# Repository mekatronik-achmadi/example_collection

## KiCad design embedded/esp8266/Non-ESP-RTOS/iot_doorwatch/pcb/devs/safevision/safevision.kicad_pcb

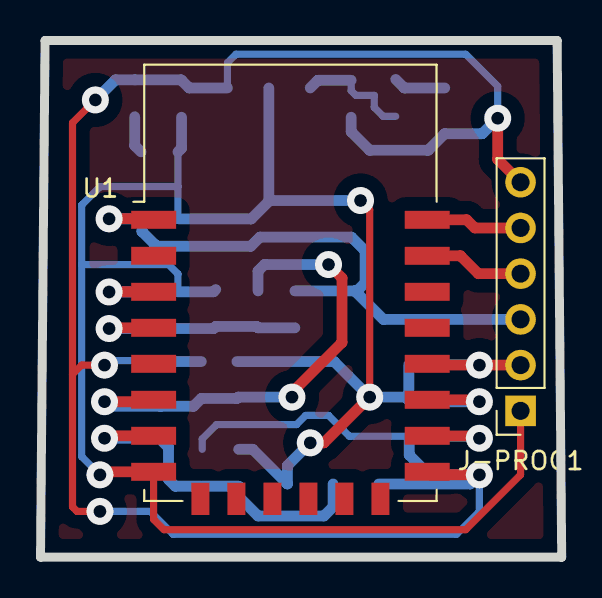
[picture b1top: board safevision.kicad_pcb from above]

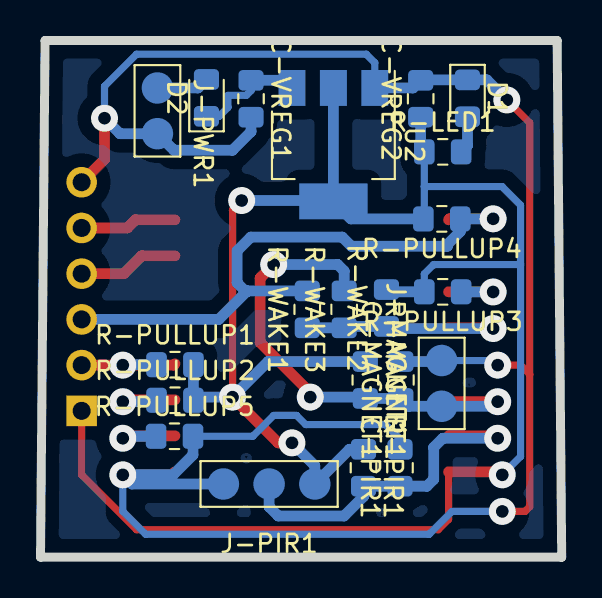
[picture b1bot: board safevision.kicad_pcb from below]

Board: 2 copper layers, 29.0 x 28.7 mm, 23 parts (21 on the bottom side), 15 nets.

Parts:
C-MAGNET1: C; C_0805_2012Metric_Pad1.15x1.40mm_HandSolder
C-PIR1: C; C_0805_2012Metric_Pad1.15x1.40mm_HandSolder
C-VREG1, C-VREG2: C; C_0805_2012Metric_Pad1.15x1.40mm_HandSolder
D1: LED; LED_0805_2012Metric_Pad1.15x1.40mm_HandSolder
D2: D; D_0805_2012Metric_Pad1.15x1.40mm_HandSolder
J-MAGNET1: Conn_01x02_Male; solderpads_small_1x2
J-PIR1: Conn_01x03_Male; solderpads_small_1x3
J-PROG1: Conn_01x06_Male; PinSocket_1x06_P2.54mm_Vertical
J-PWR1: Conn_01x02_Male; solderpads_small_1x2
R-LED1: 330; R_0805_2012Metric_Pad1.15x1.40mm_HandSolder
R-MAGNET1: 10K; R_0805_2012Metric_Pad1.15x1.40mm_HandSolder
R-PIR1: 10k; R_0805_2012Metric_Pad1.15x1.40mm_HandSolder
R-PULLUP1, R-PULLUP2, R-PULLUP3, R-PULLUP4, R-PULLUP5: 10K; R_0805_2012Metric_Pad1.15x1.40mm_HandSolder
R-WAKE1, R-WAKE3: 0; R_0805_2012Metric_Pad1.15x1.40mm_HandSolder
R-WAKE2: 10K; R_0805_2012Metric_Pad1.15x1.40mm_HandSolder
U1: ESP-12E
U2: AMS1117-3.3; SOT-223-3_TabPin2

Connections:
/EN: R-PULLUP3.1, U1.3
/MAGNET: C-MAGNET1.1, J-MAGNET1.1, R-MAGNET1.2, R-WAKE3.2, U1.6
/P0: J-PROG1.2, R-PULLUP1.1, U1.18
/P2: R-PULLUP2.1, U1.17
/P15: R-PULLUP5.1, U1.16
/PIR: C-PIR1.1, J-PIR1.2, R-PIR1.2, U1.7
/RST: J-PROG1.3, R-PULLUP4.1, R-WAKE1.2, U1.1
/RX: J-PROG1.4, U1.21
/TX: J-PROG1.5, U1.22
/WAKE: R-WAKE1.1, R-WAKE2.1, R-WAKE3.1, U1.4
GND: C-MAGNET1.2, C-PIR1.2, C-VREG1.2, C-VREG2.2, D1.1, J-MAGNET1.2, J-PIR1.3, J-PROG1.6, J-PWR1.2, R-PULLUP5.2, U1.15, U2.1
unnamed: C-VREG1.1, D2.1, U2.3
unnamed: D1.2, R-LED1.2
unnamed: D2.2, J-PWR1.1
VDD: C-VREG2.1, J-PIR1.1, J-PROG1.1, R-LED1.1, R-MAGNET1.1, R-PIR1.1, R-PULLUP1.2, R-PULLUP2.2, R-PULLUP3.2, R-PULLUP4.2, R-WAKE2.2, U1.8, U2.2

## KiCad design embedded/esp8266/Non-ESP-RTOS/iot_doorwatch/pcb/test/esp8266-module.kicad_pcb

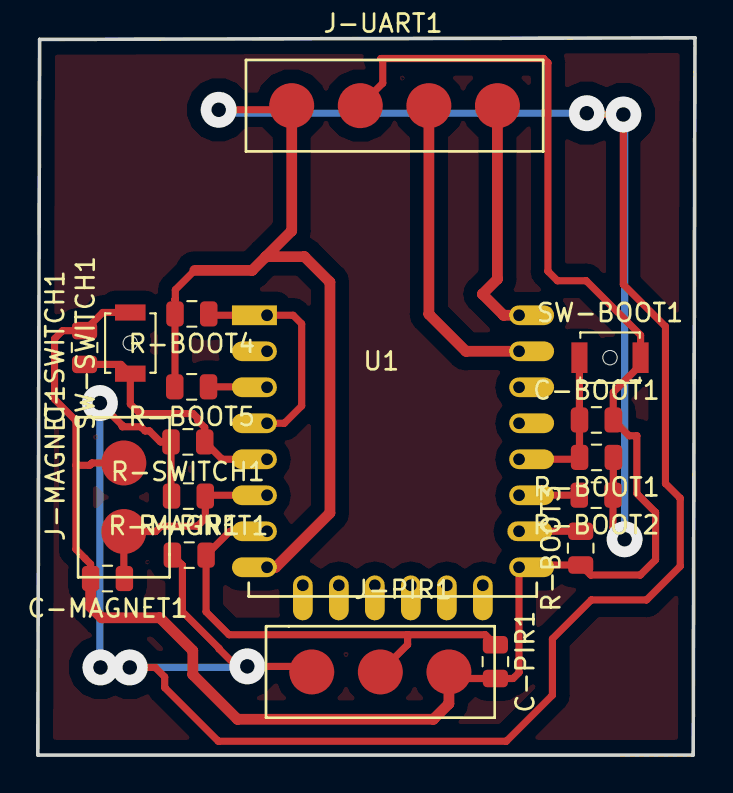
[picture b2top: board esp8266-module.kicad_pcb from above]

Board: 2 copper layers, 36.5 x 39.8 mm, 18 parts (0 on the bottom side), 12 nets.

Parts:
C-BOOT1: C; C_0805_2012Metric
C-MAGNET1: C; C_0805_2012Metric
C-PIR1: C; C_0805_2012Metric
C-SWITCH1: C; C_0805_2012Metric
J-MAGNET1: Conn_01x02_Male; solderpads_1x2
J-PIR1: Conn_01x03_Male; solderpads_1x3
J-UART1: Conn_01x04_Male; solderpads_1x4
R-BOOT1, R-BOOT2, R-BOOT3, R-BOOT4, R-BOOT5: 10K; R_0805_2012Metric
R-MAGNET1: 10K; R_0805_2012Metric
R-PIR1: 10K; R_0805_2012Metric
R-SWITCH1: 10K; R_0805_2012Metric
SW-BOOT1: SW_Push; SW_SPST_B3U-1000P-B
SW-SWITCH1: SW_Push; SW_SPST_B3U-1000P-B
U1: ESP-12E

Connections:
/GPIO_0: C-BOOT1.1, R-BOOT1.2, SW-BOOT1.1, U1.12
/GPIO_12: C-MAGNET1.1, J-MAGNET1.1, R-MAGNET1.1, U1.6
/GPIO_13: C-PIR1.1, J-PIR1.2, R-PIR1.2, U1.7
/GPIO_14: C-SWITCH1.1, R-SWITCH1.1, SW-SWITCH1.1, U1.5
/RX: J-UART1.3, U1.15
/TX: J-UART1.4, U1.16
/nRST: R-BOOT4.1, U1.1, U1.4
GND: C-BOOT1.2, C-MAGNET1.2, C-PIR1.2, C-SWITCH1.2, J-MAGNET1.2, J-PIR1.3, J-UART1.2, R-BOOT3.1, SW-BOOT1.2, SW-SWITCH1.2, U1.9
unnamed: R-BOOT2.2, U1.11
unnamed: R-BOOT3.2, U1.10
unnamed: R-BOOT5.1, U1.3
VDD: J-PIR1.1, J-UART1.1, R-BOOT1.1, R-BOOT2.1, R-BOOT4.2, R-BOOT5.2, R-MAGNET1.2, R-PIR1.1, R-SWITCH1.2, U1.8

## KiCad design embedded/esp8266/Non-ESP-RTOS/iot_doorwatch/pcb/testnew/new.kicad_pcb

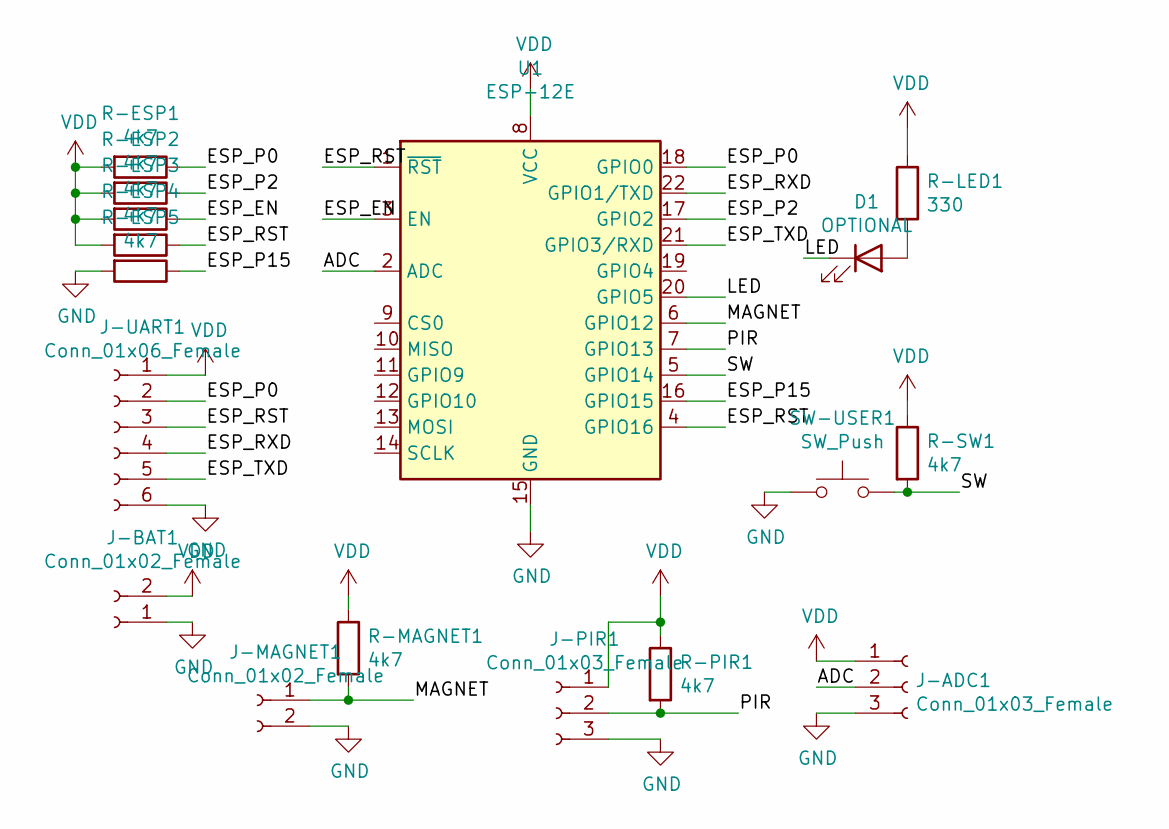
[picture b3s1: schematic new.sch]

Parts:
D1: OPTIONAL; LED_0805_2012Metric_Pad1.15x1.40mm_HandSolder
J-ADC1: Conn_01x03_Female; PinHeader_1x03_P1.27mm_Vertical
J-BAT1: Conn_01x02_Female; PinHeader_1x02_P1.27mm_Vertical
J-MAGNET1: Conn_01x02_Female; PinHeader_1x02_P1.27mm_Vertical
J-PIR1: Conn_01x03_Female; PinHeader_1x03_P1.27mm_Vertical
J-UART1: Conn_01x06_Female; PinHeader_1x06_P1.27mm_Vertical
R-ESP1, R-ESP2, R-ESP3, R-ESP4, R-ESP5: 4k7; R_0805_2012Metric_Pad1.15x1.40mm_HandSolder
R-LED1: 330; R_0805_2012Metric_Pad1.15x1.40mm_HandSolder
R-MAGNET1: 4k7; R_0805_2012Metric_Pad1.15x1.40mm_HandSolder
R-PIR1: 4k7; R_0805_2012Metric_Pad1.15x1.40mm_HandSolder
R-SW1: 4k7; R_0805_2012Metric_Pad1.15x1.40mm_HandSolder
SW-USER1: SW_Push; SW_SPST_B3U-1000P-B
U1: ESP-12E

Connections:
/ADC: J-ADC1.2, U1.2 (ADC)
/ESP_EN: R-ESP3.1, U1.3 (EN)
/ESP_P0: J-UART1.2, R-ESP1.1, U1.18 (GPIO0)
/ESP_P2: R-ESP2.1, U1.17 (GPIO2)
/ESP_P15: R-ESP5.1, U1.16 (GPIO15)
/ESP_RST: J-UART1.3, R-ESP4.1, U1.1 (~RST), U1.4 (GPIO16)
/ESP_RXD: J-UART1.4, U1.22 (GPIO1/TXD)
/ESP_TXD: J-UART1.5, U1.21 (GPIO3/RXD)
/LED: D1.1 (K), U1.20 (GPIO5)
/MAGNET: J-MAGNET1.1, R-MAGNET1.2, U1.6 (GPIO12)
/PIR: J-PIR1.2, R-PIR1.2, U1.7 (GPIO13)
/SW: R-SW1.2, SW-USER1.2, U1.5 (GPIO14)
GND: J-ADC1.3, J-BAT1.1, J-MAGNET1.2, J-PIR1.3, J-UART1.6, R-ESP5.2, SW-USER1.1, U1.15 (GND)
unnamed: D1.2 (A), R-LED1.2
VDD: J-ADC1.1, J-BAT1.2, J-PIR1.1, J-UART1.1, R-ESP1.2, R-ESP2.2, R-ESP3.2, R-ESP4.2, R-LED1.1, R-MAGNET1.1, R-PIR1.1, R-SW1.1, U1.8 (VCC)

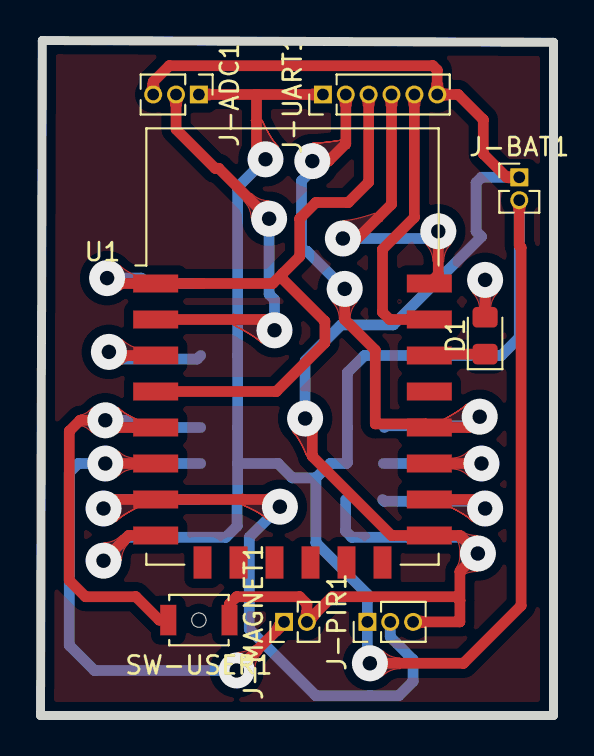
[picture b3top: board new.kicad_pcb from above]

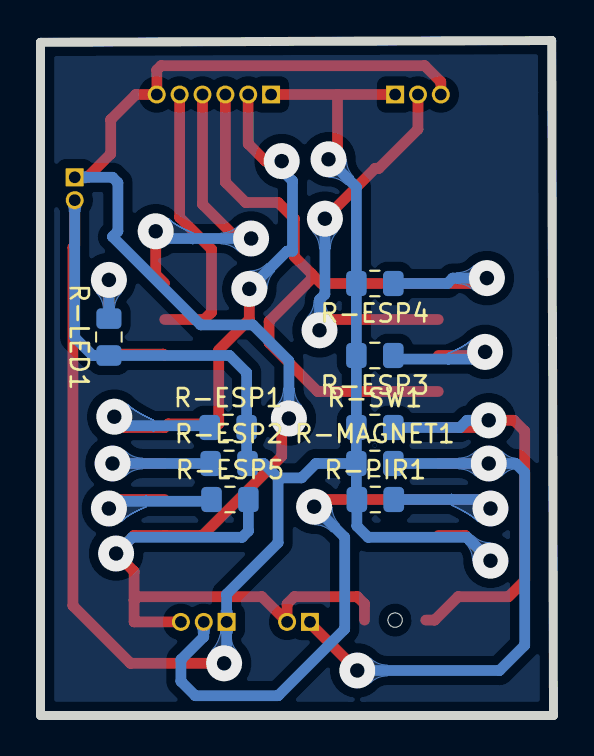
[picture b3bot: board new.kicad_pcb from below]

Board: 2 copper layers, 28.5 x 37.5 mm, 17 parts (9 on the bottom side), 15 nets.

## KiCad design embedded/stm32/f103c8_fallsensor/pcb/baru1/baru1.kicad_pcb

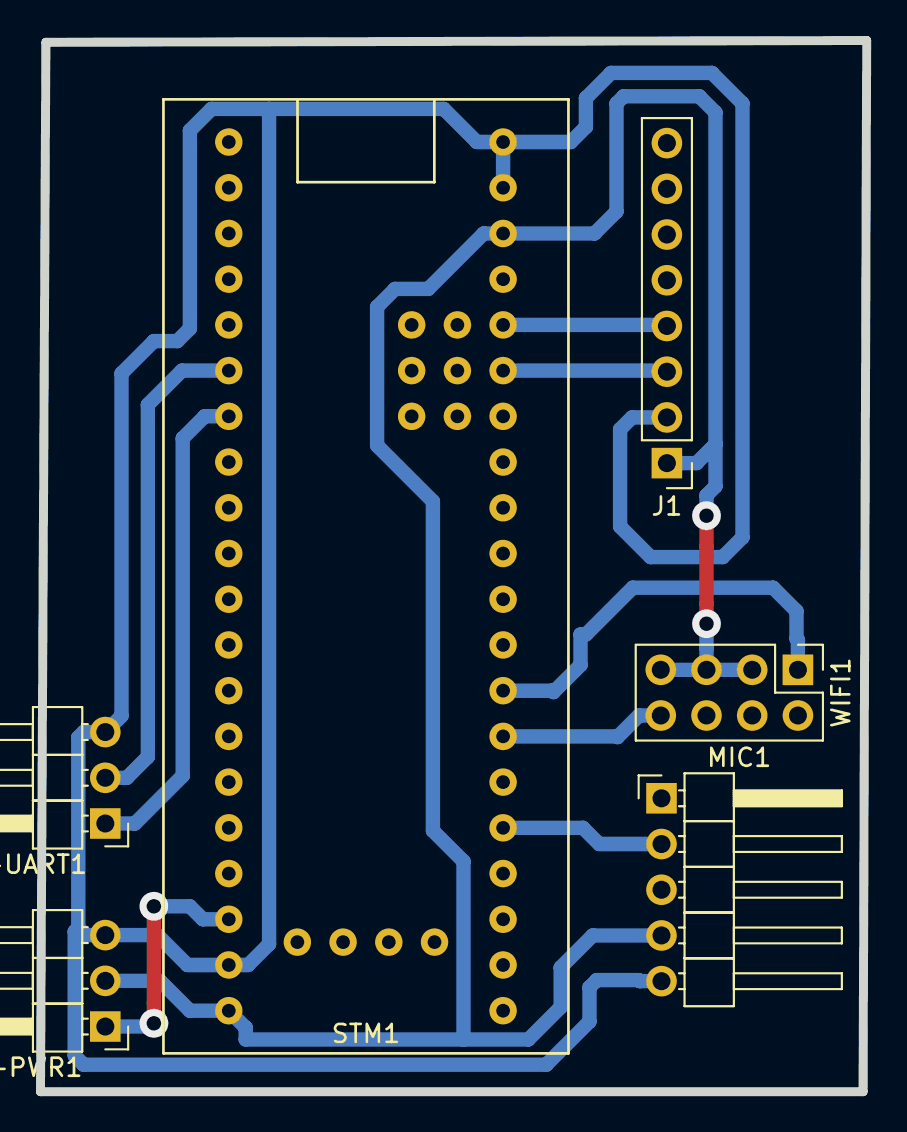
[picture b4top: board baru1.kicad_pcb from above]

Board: 2 copper layers, 45.9 x 58.4 mm, 6 parts (0 on the bottom side), 10 nets.

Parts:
J1: CONN_01X08; Pin_Header_Straight_1x08_Pitch2.54mm
J-PWR1: CONN_01X03; Pin_Header_Angled_1x03_Pitch2.54mm
J-UART1: CONN_01X03; Pin_Header_Angled_1x03_Pitch2.54mm
MIC1: CONN_01X05; Pin_Header_Angled_1x05_Pitch2.54mm
STM1: BP; BLUEPILL
WIFI1: CONN_02X04; Pin_Header_Straight_2x04_Pitch2.54mm

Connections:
+3V3: J1.1, J-PWR1.2, MIC1.4, STM1.3V3, WIFI1.3, WIFI1.5, WIFI1.7
+5V: J-PWR1.1, STM1.5V
FT_RX: J-UART1.1, STM1.PA10
FT_TX: J-UART1.2, STM1.PA9
GND: J1.2, J-PWR1.3, J-UART1.3, MIC1.5, STM1.G, WIFI1.2
MIC: MIC1.2, STM1.PA0
RX: STM1.PA2, WIFI1.8
SCL: J1.3, STM1.PB10
SDA: J1.4, STM1.PB11
TX: STM1.PA3, WIFI1.1
